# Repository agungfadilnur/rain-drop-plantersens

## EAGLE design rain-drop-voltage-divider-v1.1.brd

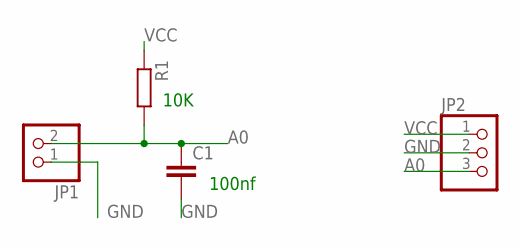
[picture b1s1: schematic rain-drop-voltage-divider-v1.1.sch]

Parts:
C1: C2.5/2; C2.5-2
JP1: PINHD-1X2; 1X02
JP2: PINHD-1X3; 1X03
R1: R-EU_0204/7; 0204/7

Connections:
A0: C1.1, JP1.2, JP2.3, R1.2
GND: C1.2, JP1.1, JP2.2
VCC: JP2.1, R1.1

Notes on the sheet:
10K
100nf

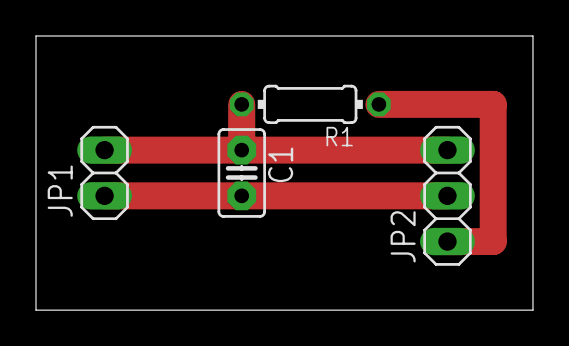
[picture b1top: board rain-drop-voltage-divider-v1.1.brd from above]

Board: 2 copper layers, 27.6 x 15.2 mm, 4 parts (0 on the bottom side), 3 nets.
